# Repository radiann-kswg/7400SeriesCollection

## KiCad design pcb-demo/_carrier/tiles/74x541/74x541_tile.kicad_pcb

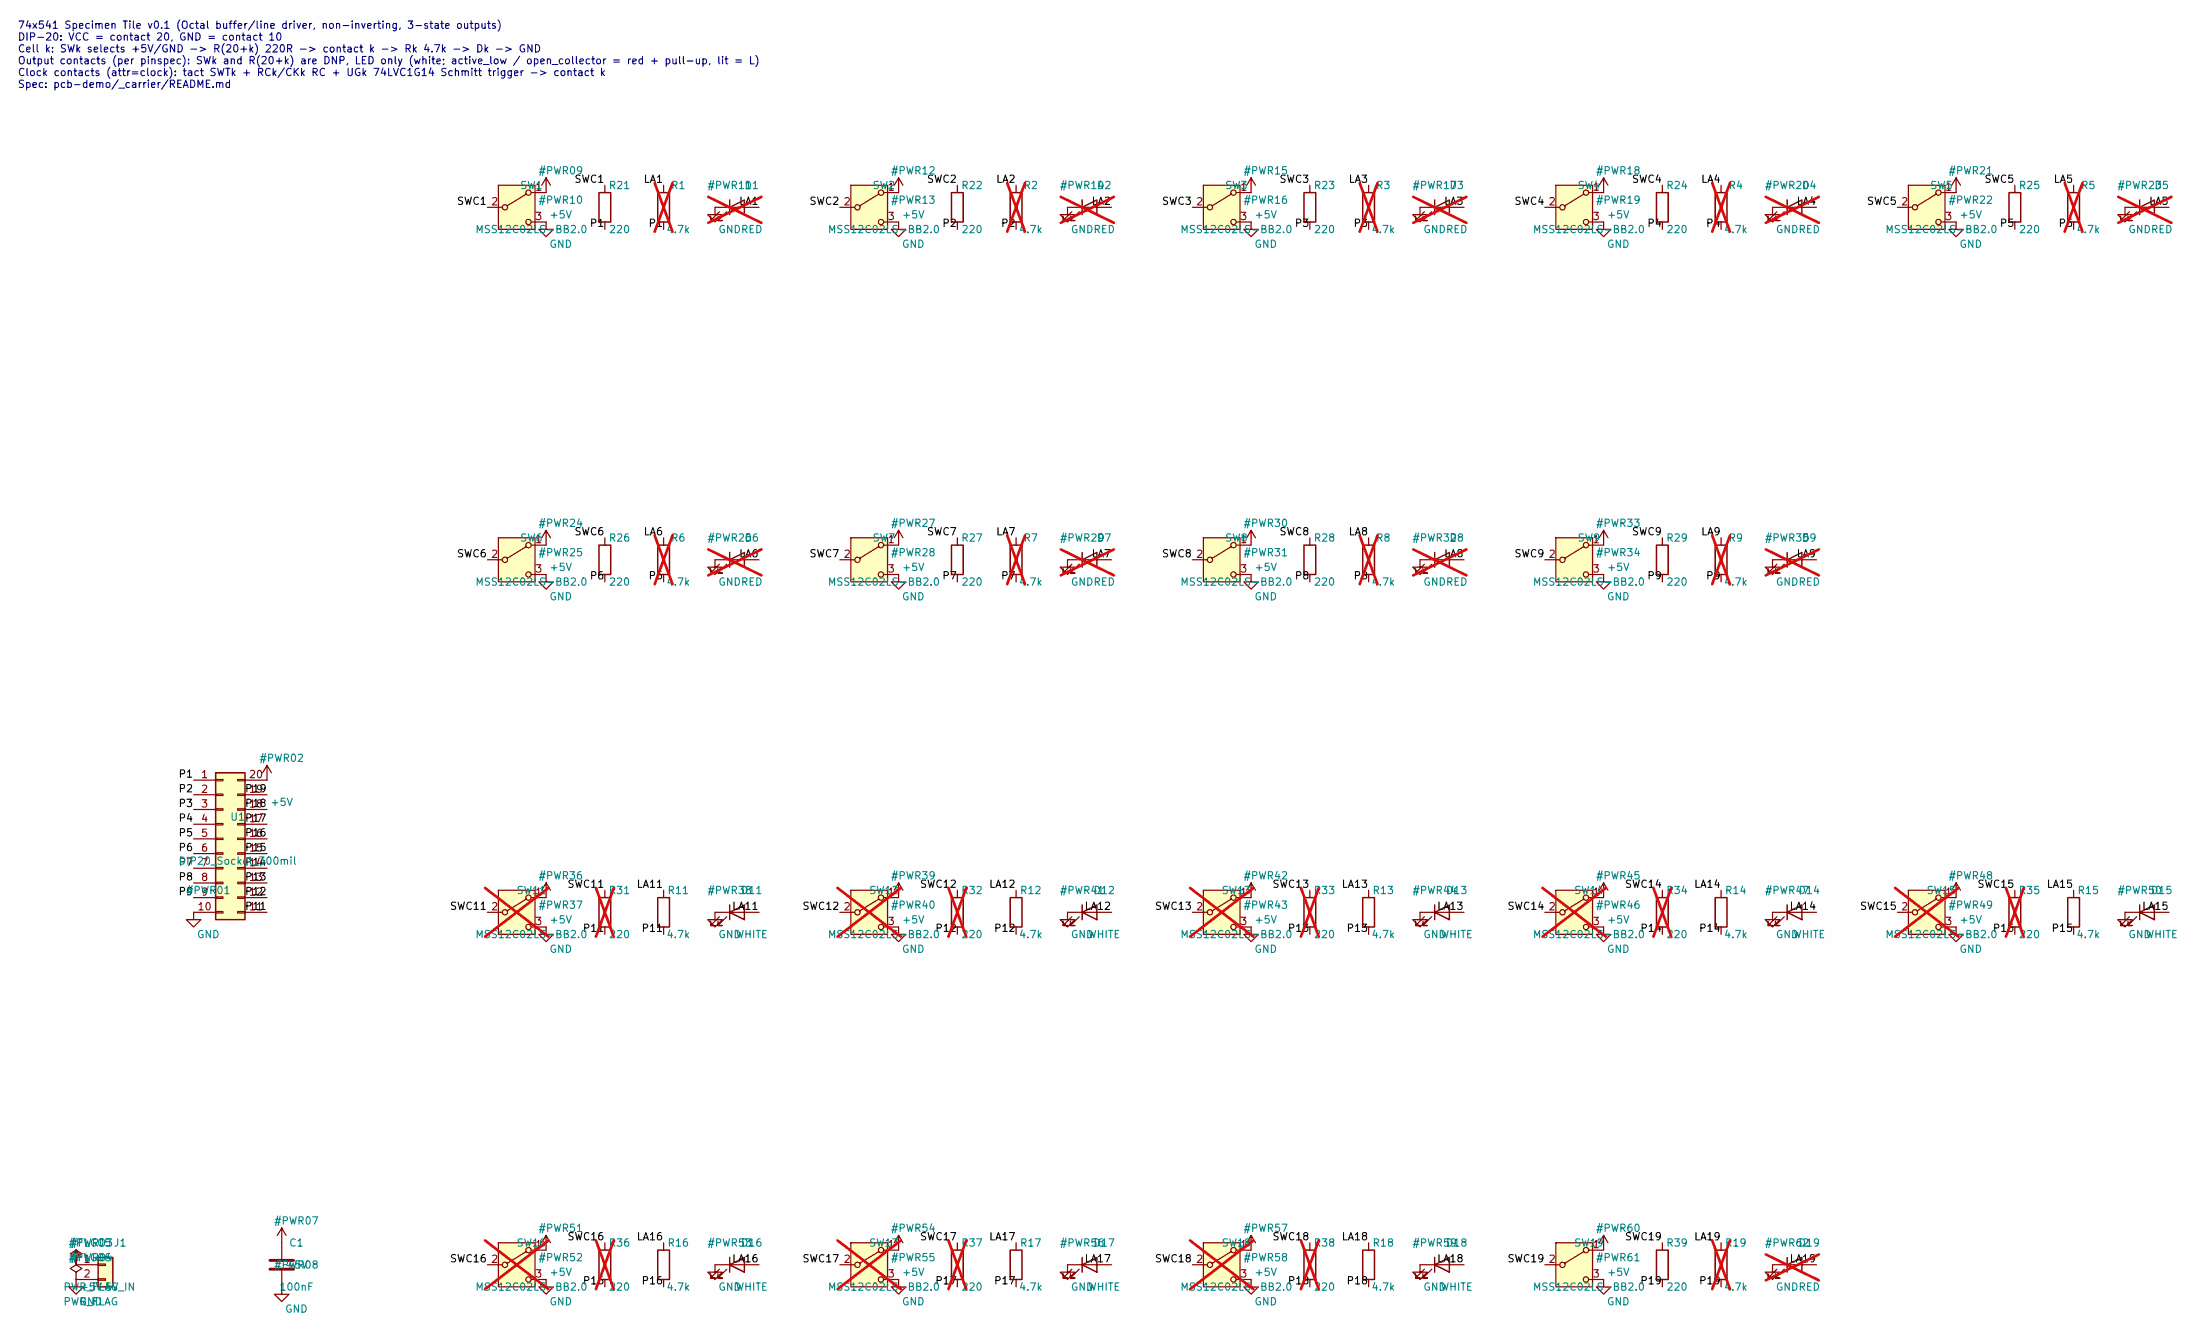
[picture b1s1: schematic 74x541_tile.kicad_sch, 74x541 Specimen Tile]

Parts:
C1: 100nF; C_0603_1608Metric; MPN CC0603KRX7R9BB104; LCSC Part # C14663
D1, D2, D3, D4, D5, D6, D7, D8, D9, D19: RED; LED_0603_1608Metric; MPN KT-0603R; LCSC Part # C2286; not fitted
D11, D12, D13, D14, D15, D16, D17, D18: WHITE; LED_0603_1608Metric; MPN KT-0603W; LCSC Part # C2290
J1: 5V_IN; PinHeader_1x02_P2.54mm_Vertical
R1, R2, R3, R4, R5, R6, R7, R8, R9, R19: 4.7k; R_0603_1608Metric; MPN 0603WAF4701T5E; LCSC Part # C23162; not fitted
R11, R12, R13, R14, R15, R16, R17, R18: 4.7k; R_0603_1608Metric; MPN 0603WAF4701T5E; LCSC Part # C23162
R21, R22, R23, R24, R25, R26, R27, R28, R29, R39: 220; R_0603_1608Metric; MPN 0603WAF2200T5E; LCSC Part # C22962
R31, R32, R33, R34, R35, R36, R37, R38: 220; R_0603_1608Metric; MPN 0603WAF2200T5E; LCSC Part # C22962; not fitted
SW1, SW2, SW3, SW4, SW5, SW6, SW7, SW8, SW9, SW19: MSS12C02LS-BB2.0; SW_SPDT_Shouhan_MSS12C02LS; MPN MSS12C02LS-BB2.0; LCSC Part # C3008585
SW11, SW12, SW13, SW14, SW15, SW16, SW17, SW18: MSS12C02LS-BB2.0; SW_SPDT_Shouhan_MSS12C02LS; MPN MSS12C02LS-BB2.0; LCSC Part # C3008585; not fitted
U1: DIP20_Socket_300mil; DIP-20_W7.62mm_Socket

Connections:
+5V: C1.1, J1.1, SW1.1 (A), SW2.1 (A), SW3.1 (A), SW4.1 (A), SW5.1 (A), SW6.1 (A), SW7.1 (A), SW8.1 (A), SW9.1 (A), SW11.1 (A), SW12.1 (A), SW13.1 (A), SW14.1 (A), SW15.1 (A), SW16.1 (A), SW17.1 (A), SW18.1 (A), SW19.1 (A), U1.20
/LA1: D1.2 (A), R1.1
/LA2: D2.2 (A), R2.1
/LA3: D3.2 (A), R3.1
/LA4: D4.2 (A), R4.1
/LA5: D5.2 (A), R5.1
/LA6: D6.2 (A), R6.1
/LA7: D7.2 (A), R7.1
/LA8: D8.2 (A), R8.1
/LA9: D9.2 (A), R9.1
/LA11: D11.2 (A), R11.1
/LA12: D12.2 (A), R12.1
/LA13: D13.2 (A), R13.1
/LA14: D14.2 (A), R14.1
/LA15: D15.2 (A), R15.1
/LA16: D16.2 (A), R16.1
/LA17: D17.2 (A), R17.1
/LA18: D18.2 (A), R18.1
/LA19: D19.2 (A), R19.1
/P1: R1.2, R21.2, U1.1
/P2: R2.2, R22.2, U1.2
/P3: R3.2, R23.2, U1.3
/P4: R4.2, R24.2, U1.4
/P5: R5.2, R25.2, U1.5
/P6: R6.2, R26.2, U1.6
/P7: R7.2, R27.2, U1.7
/P8: R8.2, R28.2, U1.8
/P9: R9.2, R29.2, U1.9
/P11: R11.2, R31.2, U1.11
/P12: R12.2, R32.2, U1.12
/P13: R13.2, R33.2, U1.13
/P14: R14.2, R34.2, U1.14
/P15: R15.2, R35.2, U1.15
/P16: R16.2, R36.2, U1.16
/P17: R17.2, R37.2, U1.17
/P18: R18.2, R38.2, U1.18
/P19: R19.2, R39.2, U1.19
/SWC1: R21.1, SW1.2 (B)
/SWC2: R22.1, SW2.2 (B)
/SWC3: R23.1, SW3.2 (B)
/SWC4: R24.1, SW4.2 (B)
/SWC5: R25.1, SW5.2 (B)
/SWC6: R26.1, SW6.2 (B)
/SWC7: R27.1, SW7.2 (B)
/SWC8: R28.1, SW8.2 (B)
/SWC9: R29.1, SW9.2 (B)
/SWC11: R31.1, SW11.2 (B)
/SWC12: R32.1, SW12.2 (B)
/SWC13: R33.1, SW13.2 (B)
/SWC14: R34.1, SW14.2 (B)
/SWC15: R35.1, SW15.2 (B)
/SWC16: R36.1, SW16.2 (B)
/SWC17: R37.1, SW17.2 (B)
/SWC18: R38.1, SW18.2 (B)
/SWC19: R39.1, SW19.2 (B)
GND: C1.2, D1.1 (K), D2.1 (K), D3.1 (K), D4.1 (K), D5.1 (K), D6.1 (K), D7.1 (K), D8.1 (K), D9.1 (K), D11.1 (K), D12.1 (K), D13.1 (K), D14.1 (K), D15.1 (K), D16.1 (K), D17.1 (K), D18.1 (K), D19.1 (K), J1.2, SW1.3 (C), SW2.3 (C), SW3.3 (C), SW4.3 (C), SW5.3 (C), SW6.3 (C), SW7.3 (C), SW8.3 (C), SW9.3 (C), SW11.3 (C), SW12.3 (C), SW13.3 (C), SW14.3 (C), SW15.3 (C), SW16.3 (C), SW17.3 (C), SW18.3 (C), SW19.3 (C), U1.10

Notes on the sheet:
74x541 Specimen Tile v0.1 (Octal buffer/line driver, non-inverting, 3-state outputs) DIP-20: VCC = contact 20, GND = contact 10 Cell k: SWk selects +5V/GND -> R(20+k) 220R -> contact k -> Rk 4.7k -> Dk -> GND Output contacts (per pinspec): SWk and R(20+k) are DNP, LED only (white; active_low / open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

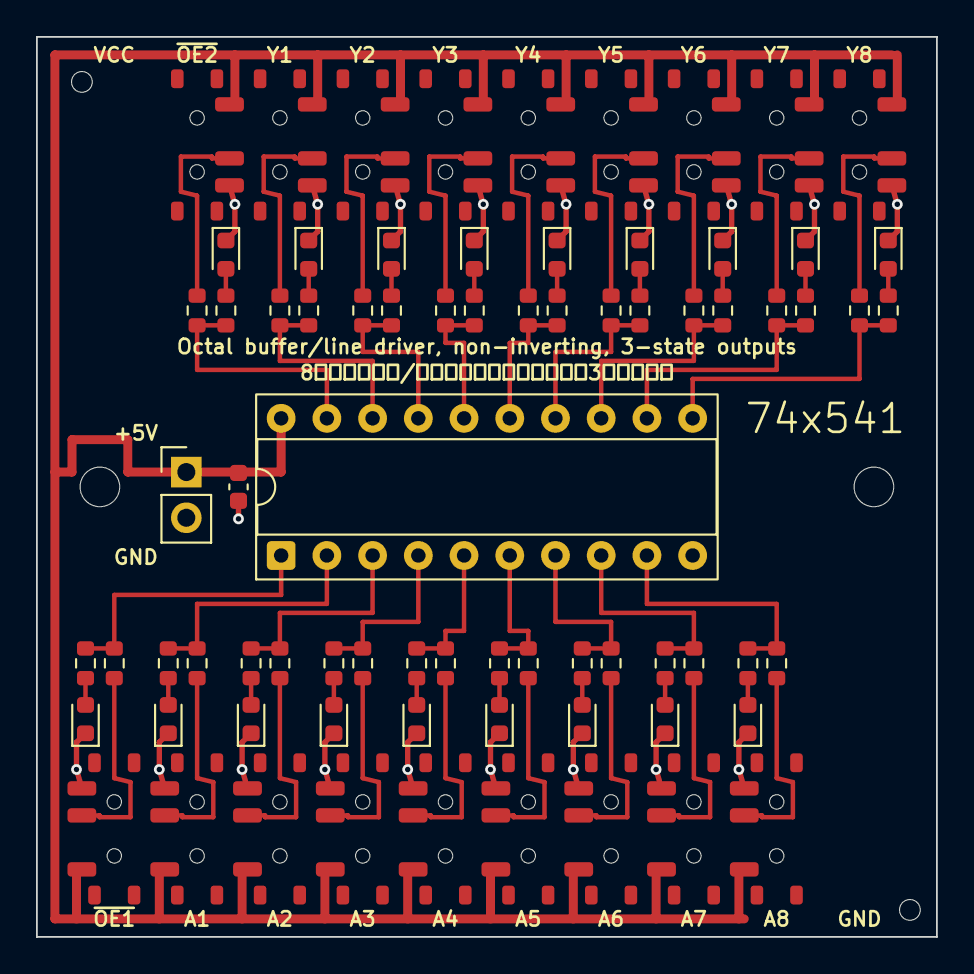
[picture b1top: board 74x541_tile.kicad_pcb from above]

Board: 2 copper layers, 50.0 x 50.0 mm, 79 parts (0 on the bottom side), 56 nets.

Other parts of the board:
MTG1, MTG2: MountingHole_2.2mm_M2
TH1, TH2: ToolingHole_1.152mm

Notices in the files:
pcb-demo/_carrier/tiles/74x541/74x541_tile.kicad_pcb:
MIT License
